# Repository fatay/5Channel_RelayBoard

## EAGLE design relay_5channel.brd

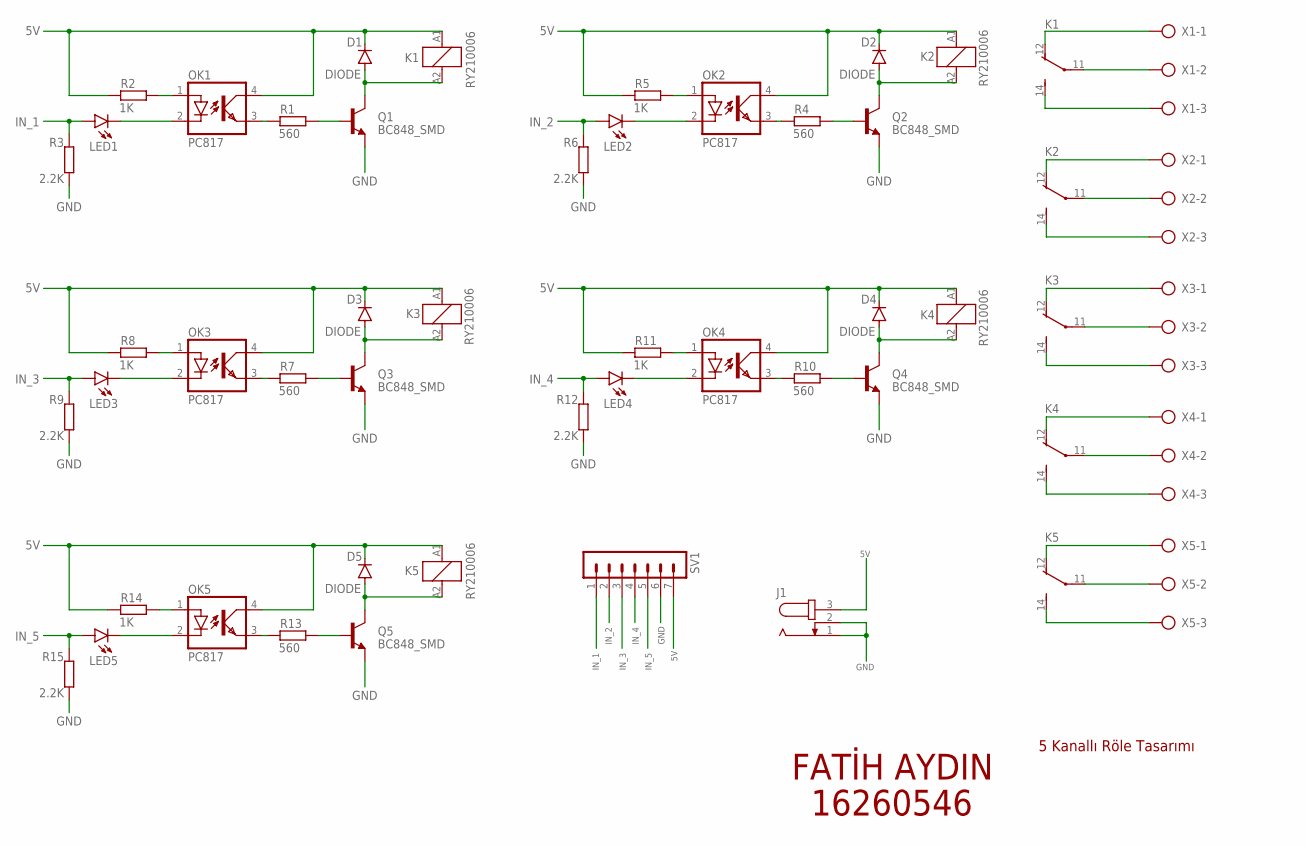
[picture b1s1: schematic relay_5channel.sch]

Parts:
D1, D2, D3, D4, D5: DIODE; DO35-7
J1: JACK-PLUG1; SPC4078
K1, K2, K3, K4, K5: RY210006; RY-II
LED1, LED2, LED3, LED4, LED5: LEDCHIP-LED0805; CHIP-LED0805
OK1, OK2, OK3, OK4, OK5: PC817; DIL04
Q1, Q2, Q3, Q4, Q5: BC848_SMD; SOT23
R1, R4, R7, R10, R13: 560; M0805
R2, R5, R8, R11, R14: 1K; 0204/5
R3, R6, R9, R12, R15: 2.2K; 0204/5
SV1: MA07-1
X1, X2, X3, X4, X5: AK300/3

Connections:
5V: D1.C, D2.C, D3.C, D4.C, D5.C, J1.3, K1.A1 (1), K2.A1 (1), K3.A1 (1), K4.A1 (1), K5.A1 (1), OK1.4 (COL), OK2.4 (COL), OK3.4 (COL), OK4.4 (COL), OK5.4 (COL), R2.1, R5.1, R8.1, R11.1, R14.1, SV1.7
COM: K1.11, X1.2
GND: J1.1, J1.2, Q1.2 (E), Q2.2 (E), Q3.2 (E), Q4.2 (E), Q5.2 (E), R3.1, R6.1, R9.1, R12.1, R15.1, SV1.6
IN_1: LED1.A, R3.2, SV1.1
IN_2: LED2.A, R6.2, SV1.2
IN_3: LED3.A, R9.2, SV1.3
IN_4: LED4.A, R12.2, SV1.4
IN_5: LED5.A, R15.2, SV1.5
unnamed: OK1.1 (A), R2.2
unnamed: LED1.C, OK1.2 (C)
unnamed: OK2.1 (A), R5.2
unnamed: Q1.1 (B), R1.2
unnamed: LED2.C, OK2.2 (C)
unnamed: OK1.3 (EMIT), R1.1
unnamed: D1.A, K1.A2 (2), Q1.3 (C)
unnamed: OK2.3 (EMIT), R4.1
unnamed: D2.A, K2.A2 (2), Q2.3 (C)
unnamed: Q2.1 (B), R4.2
unnamed: OK3.1 (A), R8.2
unnamed: LED3.C, OK3.2 (C)
unnamed: OK3.3 (EMIT), R7.1
unnamed: D3.A, K3.A2 (2), Q3.3 (C)
unnamed: Q3.1 (B), R7.2
unnamed: OK4.1 (A), R11.2
unnamed: LED4.C, OK4.2 (C)
unnamed: OK4.3 (EMIT), R10.1
unnamed: D4.A, K4.A2 (2), Q4.3 (C)
unnamed: Q4.1 (B), R10.2
unnamed: OK5.1 (A), R14.2
unnamed: LED5.C, OK5.2 (C)
unnamed: OK5.3 (EMIT), R13.1
unnamed: D5.A, K5.A2 (2), Q5.3 (C)
unnamed: Q5.1 (B), R13.2
unnamed: K2.11, X2.2
unnamed: K2.14 (S), X2.3
unnamed: K2.12 (O), X2.1
unnamed: K3.12 (O), X3.1
unnamed: K3.14 (S), X3.3
unnamed: K3.11, X3.2
unnamed: K4.12 (O), X4.1
unnamed: K4.14 (S), X4.3
unnamed: K4.11, X4.2
unnamed: K5.11, X5.2
unnamed: K5.12 (O), X5.1
unnamed: K5.14 (S), X5.3
NC: K1.12 (O), X1.1
NO: K1.14 (S), X1.3

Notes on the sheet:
FATİH AYDIN
16260546
5 Kanallı Röle Tasarımı

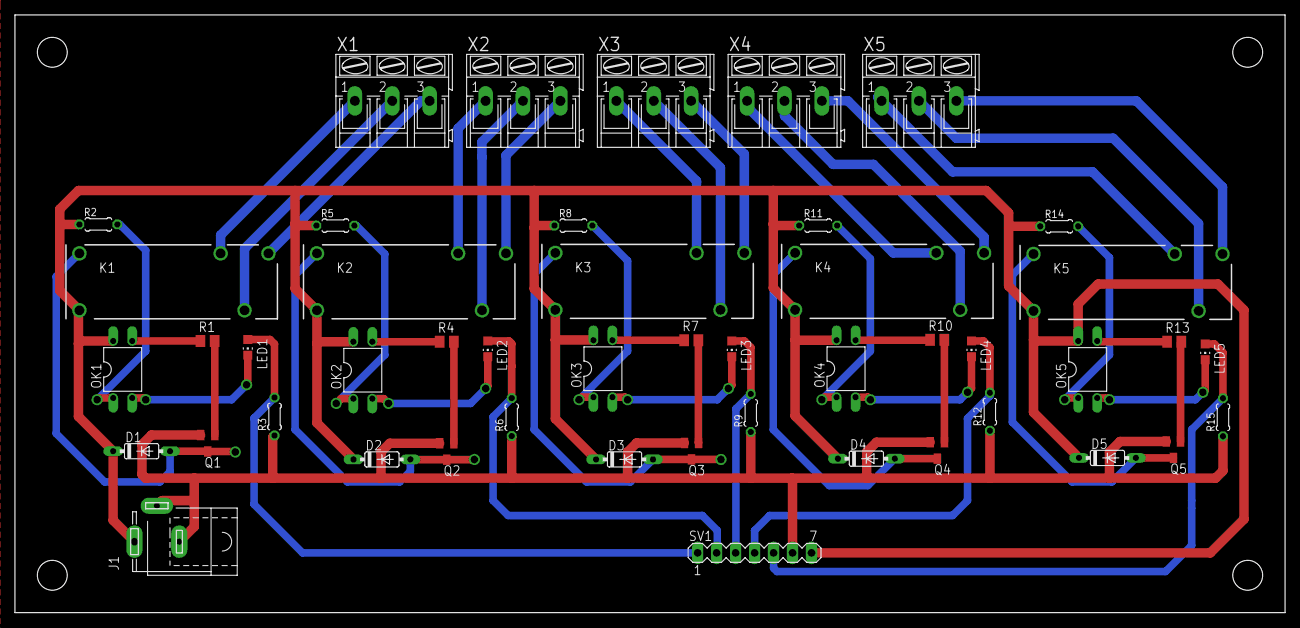
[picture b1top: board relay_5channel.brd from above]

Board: 2 copper layers, 170.0 x 80.0 mm, 47 parts (0 on the bottom side), 47 nets.

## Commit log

2020-05-22 r1
    r1r
